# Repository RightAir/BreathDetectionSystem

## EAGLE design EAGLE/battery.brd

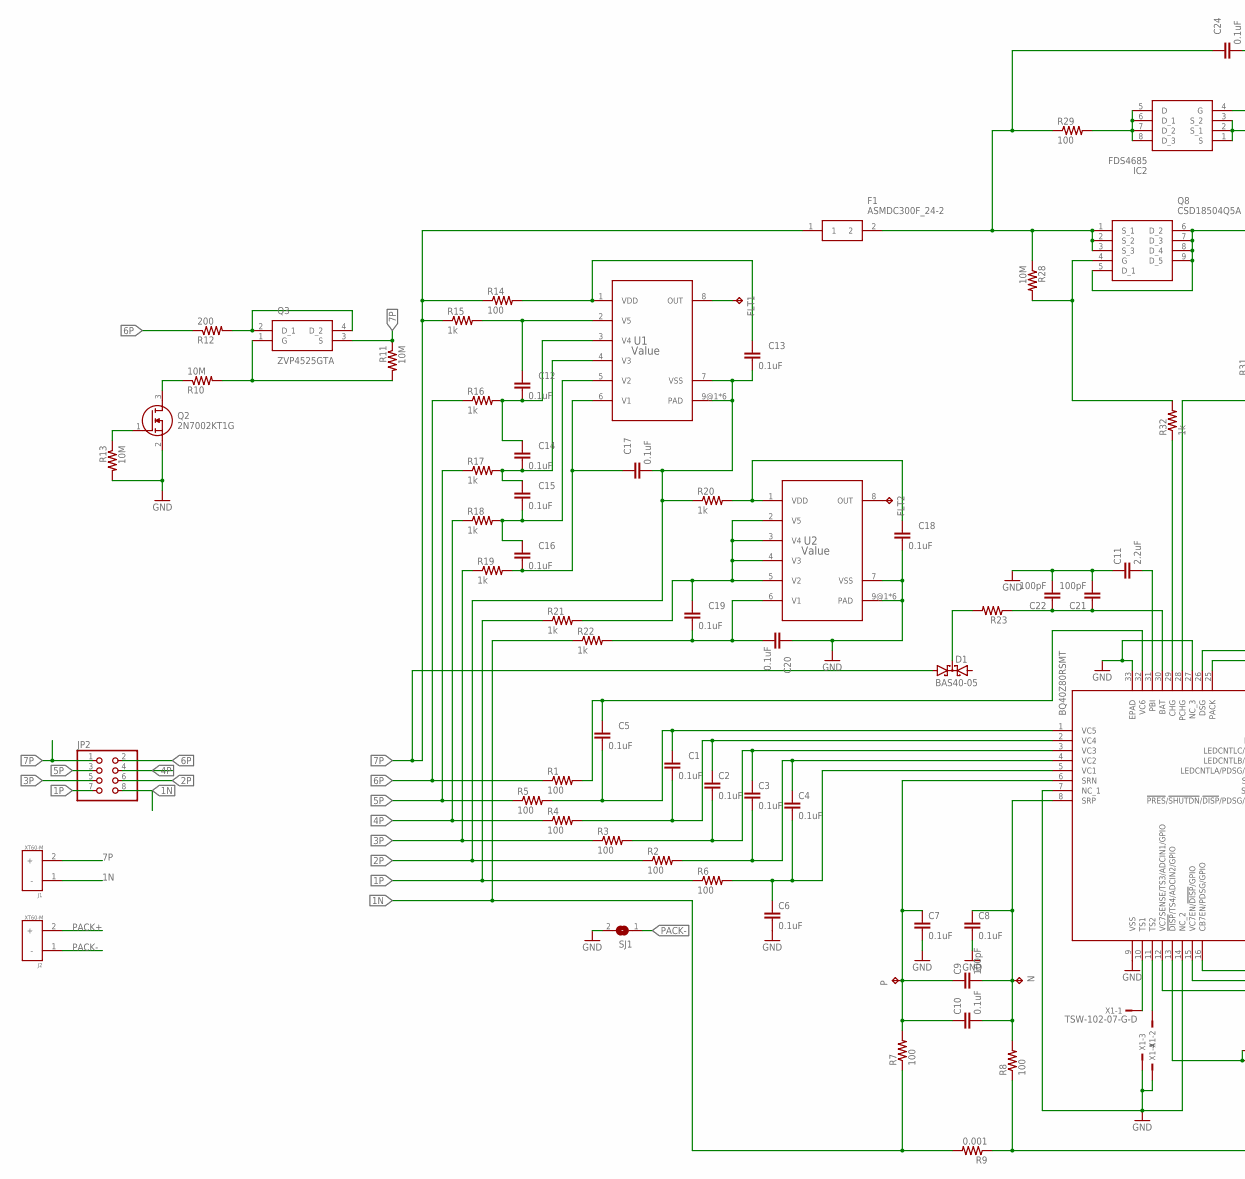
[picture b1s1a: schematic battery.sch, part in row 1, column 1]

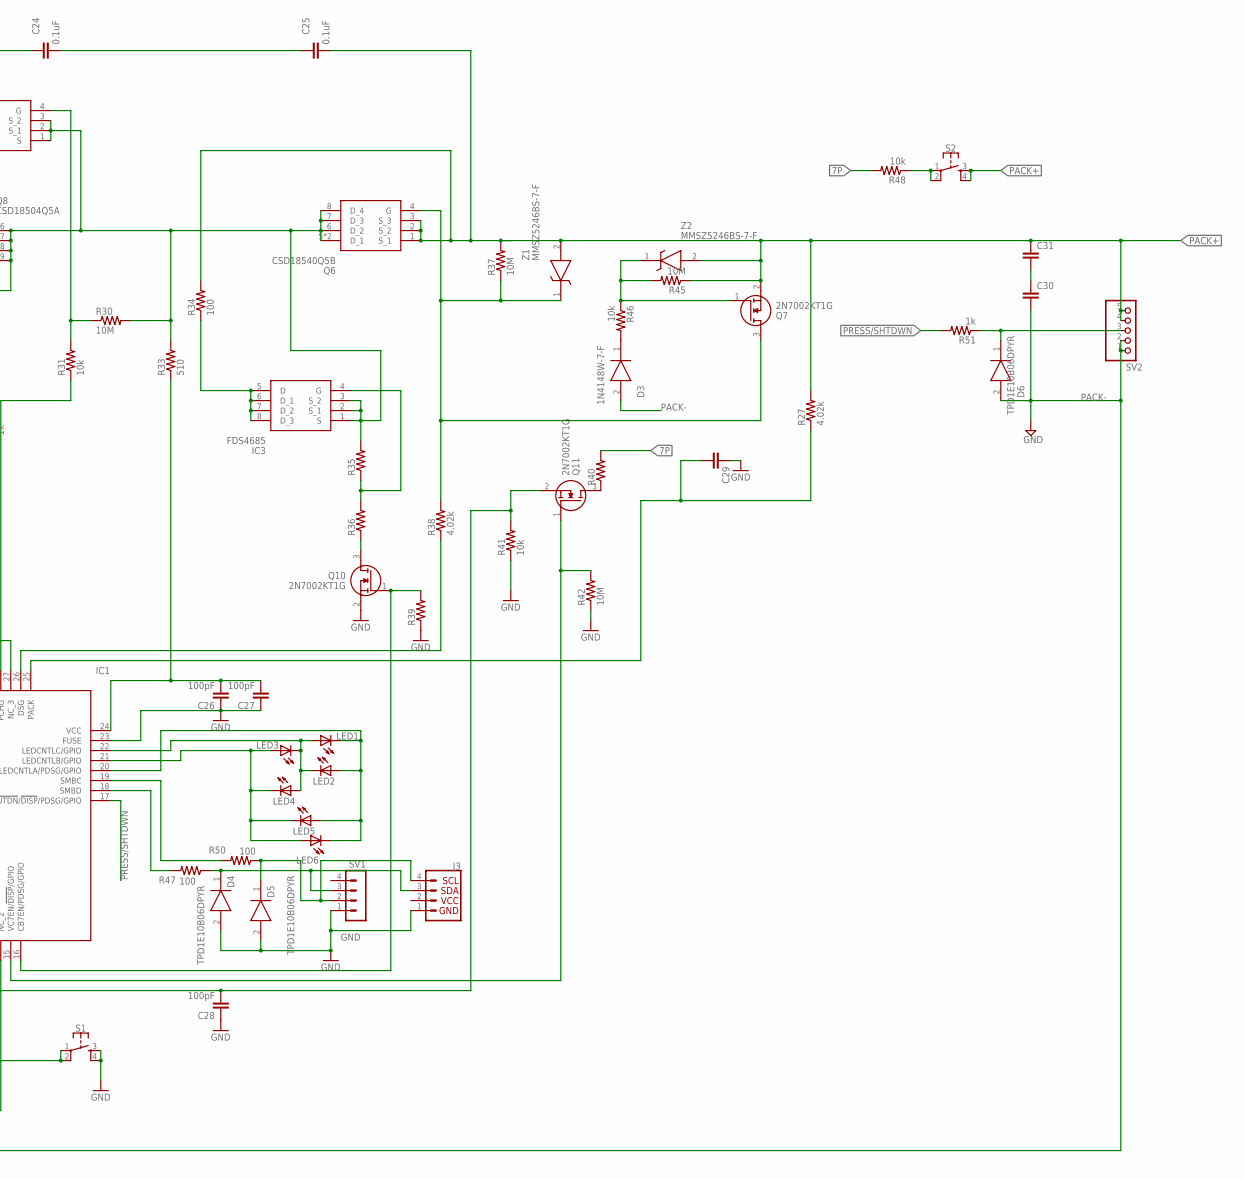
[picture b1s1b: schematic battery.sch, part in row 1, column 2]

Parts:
C1, C2, C3, C4, C5, C6, C7, C8, C10, C12, C13, C14, C15, C16, C17, C18, C19, C20, C24, C25: 0.1uF; C0603
C9, C21, C22, C26, C27, C28: 100pF; C0603
C11: 2.2uF; C1812
C29, C30, C31: C-EUC0603; C0603
D1: BAS40-05; SOT23
D3: 1N4148W-7-F; SOD3716X115N
D4, D5, D6: TPD1E10B06DPYR; DPY(R-PX1SON-N2)
F1: ASMDC300F_24-2; FUSC7551X110N
FLT1, FLT2: TPTP13R; TP13R
IC1: BQ40Z80RSMT; QFN40P400X400X100-33N
IC2, IC3: FDS4685; SOIC127P600X175-8N
J1, J2: XT60-M; AMASS_XT60-M
J3: QWIIC_CONNECTORJS-1MM; JST04_1MM_RA
JP2: PINHD-2X4; 2X04
LED1, LED2, LED3, LED4, LED5, LED6: LEDCHIPLED_0603; CHIPLED_0603
N: TPTP13R; TP13R
P: TPTP13R; TP13R
Q2, Q7, Q10, Q11: 2N7002KT1G; SOT96P237X111-3N
Q3: ZVP4525GTA; SOT230P700X180-4N
Q6: CSD18540Q5B; Q5B
Q8: CSD18504Q5A; CSD18514Q5AT
R1, R2, R3, R4, R5, R6, R7, R8, R14, R47, R50: 100; R0603
R9: 0.001; R1210
R10, R11, R13, R28, R30, R37, R42, R45: 10M; R0603
R12: 200; R0603
R15, R16, R17, R18, R19, R20, R21, R22, R32, R51: 1k; R0603
R23, R35, R36, R39, R40: R-US_R0603; R0603
R27, R38: 4.02k; R0603
R29, R34: 100; R1210
R31, R41, R46, R48: 10k; R0603
R33: 510; R0603
S1, S2: MOMENTARY-SWITCH-SPST-2-SMD-4.6X2.8MM; TACTILE_SWITCH_SMD_4.6X2.8MM
SJ1: SJ
SV1: MA04-1
SV2: PINHD-1X55X2MM; 1_05X2MM
U1, U2: Value; DPJ0008A
X1: TSW-102-07-G-D; TSW-102-XX-G-D
Z1, Z2: MMSZ5246BS-7-F; SOD2513X110N

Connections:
1N: J1.1 (-), JP2.8, R7.1, R9.2, R22.1
1P: JP2.7, R6.1, R21.1
2: J3.2
2P: C13.2, C17.2, JP2.6, R2.1, R20.1, U1.7 (VSS), U1.9@1 (PAD), U1.9@2 (PAD), U1.9@3 (PAD), U1.9@4 (PAD), U1.9@5 (PAD), U1.9@6 (PAD)
3P: JP2.5, R3.1, R19.1
4P: JP2.4, R4.1, R18.1
5P: JP2.3, R5.1, R17.1
6P: JP2.2, R1.1, R12.1, R16.1
7P: D1.1 (A1), F1.1, J1.2 (+), JP2.1, Q3.3 (S), R11.1, R14.1, R15.1, R40.2, R48.2
GND: C6.2, C7.2, C8.2, C11.1, C18.2, C20.1, C21.2, C22.2, C26.1, C27.1, C28.1, C29.1, D4.2 (GND), D5.2 (GND), IC1.7 (NC_1), IC1.9 (VSS), IC1.14 (NC_2), IC1.23 (FUSE), IC1.27 (NC_3), IC1.33 (EPAD), J3.1, Q2.2 (S), Q10.2 (S), R13.2, R39.1, R41.1, R42.1, S1.3, S1.4, SJ1.2, SV1.1, U2.7 (VSS), U2.9@1 (PAD), U2.9@2 (PAD), U2.9@3 (PAD), U2.9@4 (PAD), U2.9@5 (PAD), U2.9@6 (PAD), X1.3, X1.4
unnamed: C1.1, C5.2, IC1.1 (VC5), R5.2
unnamed: C1.2, C2.1, IC1.2 (VC4), R4.2
unnamed: C2.2, C3.1, IC1.3 (VC3), R3.2
unnamed: C3.2, C4.1, IC1.4 (VC2), R2.2
unnamed: Q2.1 (G), R13.1
unnamed: C5.1, IC1.32 (VC6), R1.2
unnamed: C4.2, C6.1, IC1.5 (VC1), R6.2
unnamed: Q3.1 (G), R10.2, R11.2
unnamed: Q2.3 (D), R10.1
unnamed: Q3.2 (D_1), Q3.4 (D_2), R12.2
unnamed: C13.1, R14.2, U1.1 (VDD)
unnamed: C12.1, R15.2, U1.2 (V5)
unnamed: C7.1, C9.1, C10.1, IC1.6 (SRN), P.TP, R7.2
unnamed: C8.1, C9.2, C10.2, IC1.8 (SRP), N.TP, R8.2
unnamed: C12.2, C14.1, R16.2, U1.3 (V4)
unnamed: C11.2, IC1.31 (PBI)
unnamed: D1.3 (C), R23.2
unnamed: C14.2, C15.1, R17.2, U1.4 (V3)
unnamed: C26.2, C27.2, IC1.24 (VCC), R33.1
unnamed: C15.2, C16.1, R18.2, U1.5 (V2)
unnamed: C21.1, C22.1, IC1.30 (BAT), R23.1
unnamed: FLT2.TP, U2.8 (OUT)
unnamed: C16.2, C17.1, R19.2, U1.6 (V1)
unnamed: C18.1, R20.2, U2.1 (VDD)
unnamed: C19.1, R21.2, U2.2 (V5), U2.3 (V4), U2.4 (V3), U2.5 (V2)
unnamed: FLT1.TP, U1.8 (OUT)
unnamed: C19.2, C20.2, R22.2, U2.6 (V1)
unnamed: C24.1, F1.2, Q8.1 (S_1), Q8.2 (S_2), Q8.3 (S_3), R28.1, R29.1
unnamed: Q8.4 (G), R28.2, R32.2
unnamed: IC2.5 (D), IC2.6 (D_1), IC2.7 (D_2), IC2.8 (D_3), R29.2
unnamed: D3.1 (K), R46.2
unnamed: C24.2, C25.1
unnamed: IC2.1 (S), IC2.2 (S_1), IC2.3 (S_2), IC3.1 (S), IC3.2 (S_1), IC3.3 (S_2), Q6.5 (D_1), Q6.6 (D_2), Q6.7 (D_3), Q6.8 (D_4), Q6.9 (D_1), Q8.5 (D_1), Q8.6 (D_2), Q8.7 (D_3), Q8.8 (D_4), Q8.9 (D_5), R30.2, R33.2, R35.2
unnamed: IC2.4 (G), R30.1, R31.2
unnamed: IC1.29 (CHG), R32.1
unnamed: IC1.28 (PCHG), R31.1
unnamed: IC3.5 (D), IC3.6 (D_1), IC3.7 (D_2), IC3.8 (D_3), R34.1
unnamed: D4.1 (I/O), J3.3, R47.1, SV1.3
unnamed: Q6.4 (G), Q7.3 (D), R37.1, R38.2, Z1.1 (K)
unnamed: IC3.4 (G), R35.1, R36.2
unnamed: Q10.3 (D), R36.1
unnamed: IC1.26 (DSG), R38.1
unnamed: IC1.16 (CB7EN/PDSG/GPIO), Q10.1 (G), R39.2
unnamed: Q11.3 (D), R40.1
unnamed: C28.2, IC1.12 (VC7SENSE/TS3/ADCIN1/GPIO), Q11.2 (S), R41.2
unnamed: IC1.15 (VC7EN/!DISP!/GPIO), Q11.1 (G), R42.2
unnamed: Q7.1 (G), R45.2, R46.1, Z2.1 (K)
unnamed: IC1.10 (TS1), X1.1
unnamed: IC1.11 (TS2), X1.2
unnamed: D5.1 (I/O), J3.4, R50.1, SV1.2
unnamed: IC1.20 (LEDCNTLA/PDSG/GPIO), LED1.C, LED2.A, LED5.A, LED6.C
unnamed: IC1.21 (LEDCNTLB/GPIO), LED3.A, LED4.C, LED5.C, LED6.A
unnamed: IC1.18 (SMBD), R47.2
unnamed: R48.1, S2.1, S2.2
unnamed: C29.2, IC1.25 (PACK), R27.1
unnamed: IC1.22 (LEDCNTLC/GPIO), LED1.A, LED2.C, LED3.C, LED4.A
unnamed: D6.1 (I/O), R51.1, SV2.3
unnamed: IC1.19 (SMBC), R50.2
unnamed: IC1.13 (!DISP!/TS4/ADCIN2/GPIO), S1.1, S1.2
unnamed: C30.1, C31.2
PACK+: C25.2, C31.1, J2.2 (+), Q6.1 (S_1), Q6.2 (S_2), Q6.3 (S_3), Q7.2 (S), R27.2, R34.2, R37.2, R45.1, S2.3, S2.4, SV2.4, SV2.5, Z1.2 (A), Z2.2 (A)
PACK-: C30.2, D3.2 (A), D6.2 (GND), J2.1 (-), R8.1, R9.1, SJ1.1, SV2.1, SV2.2
PRESS/SHTDWN: IC1.17 (!PRES!/!SHUTDN!/!DISP!/PDSG/GPIO), R51.2

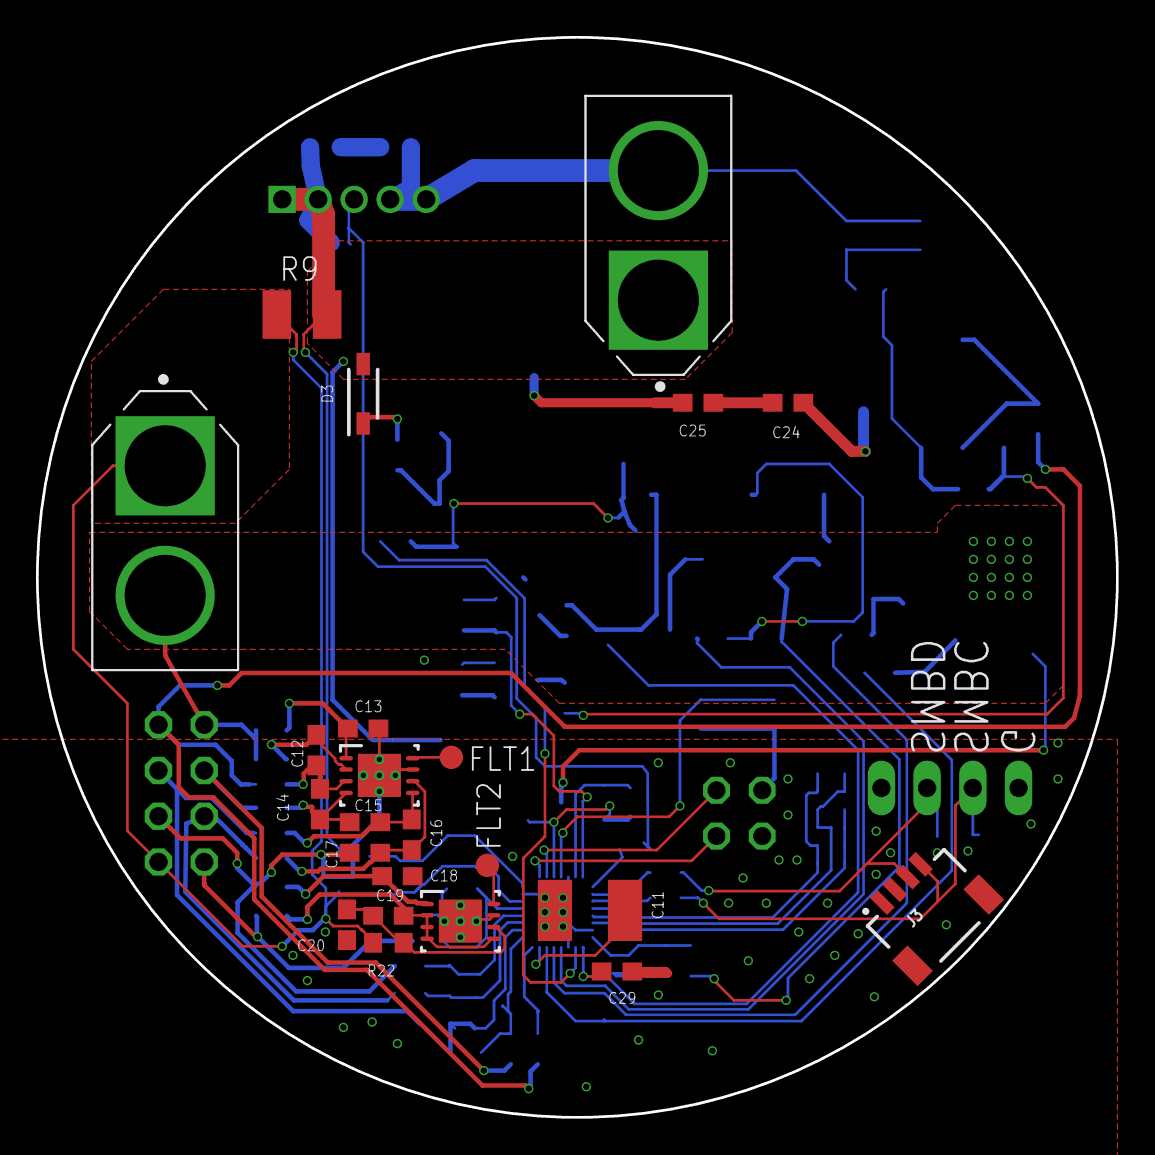
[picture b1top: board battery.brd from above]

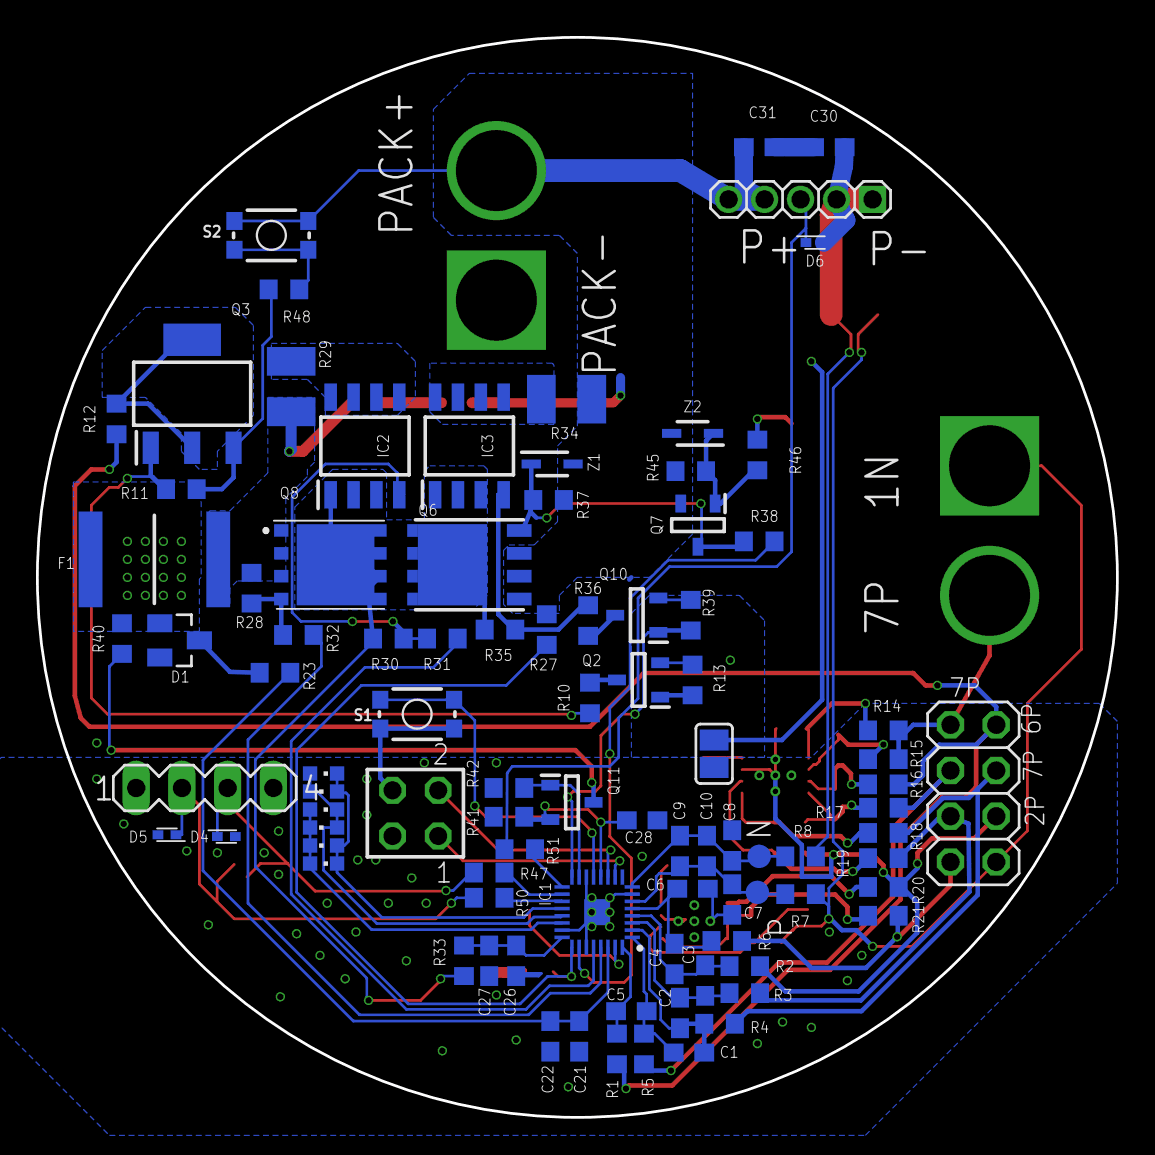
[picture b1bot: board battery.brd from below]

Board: 2 copper layers, 60.0 x 60.0 mm, 115 parts (92 on the bottom side), 72 nets.

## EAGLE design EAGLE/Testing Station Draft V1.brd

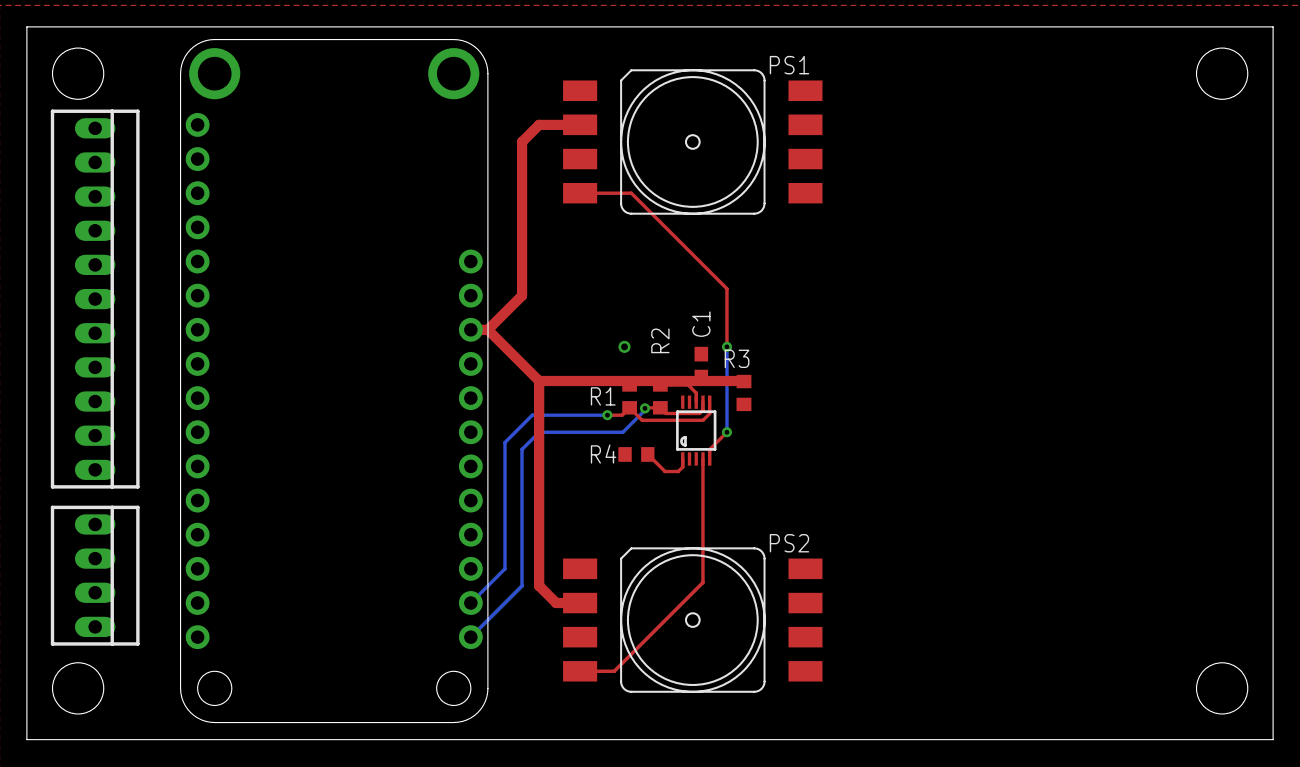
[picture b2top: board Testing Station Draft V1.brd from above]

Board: 2 copper layers, 92.7 x 53.0 mm, 11 parts (0 on the bottom side), 8 nets.

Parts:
C1: C0603
MS1: FEATHERWING
PS1, PS2: 482
R1, R2, R3, R4: R0603
U$1: ADS1015; MICROBUILDER_MSOP10
X1: 22-23-2041
X2: 22-23-2111

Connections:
+5V: PS2.2, X1.1
A0: PS2.4, U$1.4
A1: PS1.4, U$1.5
ADDR: R4.2, U$1.1
GND: C1.2, MS1.4, PS1.3, PS2.3, R4.1, U$1.3, X1.4
S$2: C1.1, R1.2, R2.2, R3.2, U$1.8
SCL: MS1.18, R1.1, U$1.6, X1.3
SDA: R2.1, U$1.7, X1.2

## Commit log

2019-08-27 Testing Station Board
2019-09-04 First TensorFlow Upload
2019-09-04 TensorFlow Sept 3
2019-09-04 Upload Breath Detection Draft
2019-09-05 TensorFlow Lite
2019-09-06 Keras Updates
2019-09-10 Decision Algorithm Draft
2019-09-10 Added change log
2019-09-10 Class Switch Updates
2019-09-13 LSTM updates / input layers
2019-09-17 Updates for LSTM
2019-09-24 Updates Sept 24
2019-09-25 Decision Algorithm Updates
2019-09-26 New Spyder files added
2019-09-26 Moving Files to Archive
2019-09-26 Sublime Update
2019-09-26 Move to Spyder
2019-09-26 Updates to Spyder
2019-09-27 Updates to decision algorithm
2019-10-07 TFLite Updates
2019-10-08 TF Updates
2019-10-10 Oct 10 Update
2019-10-10 Archive
2019-10-10 script
2019-10-10 push
2019-10-10 new script
2019-10-14 Rename script
2019-10-14 test
2019-10-14 just read
2019-10-14 sensorbus
2019-10-14 Create I2C_Notes_2
2019-10-15 Move to archive
2019-10-15 update coral test
2019-10-15 Coral Inference Updates
2019-10-16 Clean Up Files
2019-10-30 uodate

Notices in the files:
parts and their libraries:
SparkFun-Switches: Licensing: Creative Commons ShareAlike 4.0 International - https://creativecommons.org/licenses/by-sa/4.0
